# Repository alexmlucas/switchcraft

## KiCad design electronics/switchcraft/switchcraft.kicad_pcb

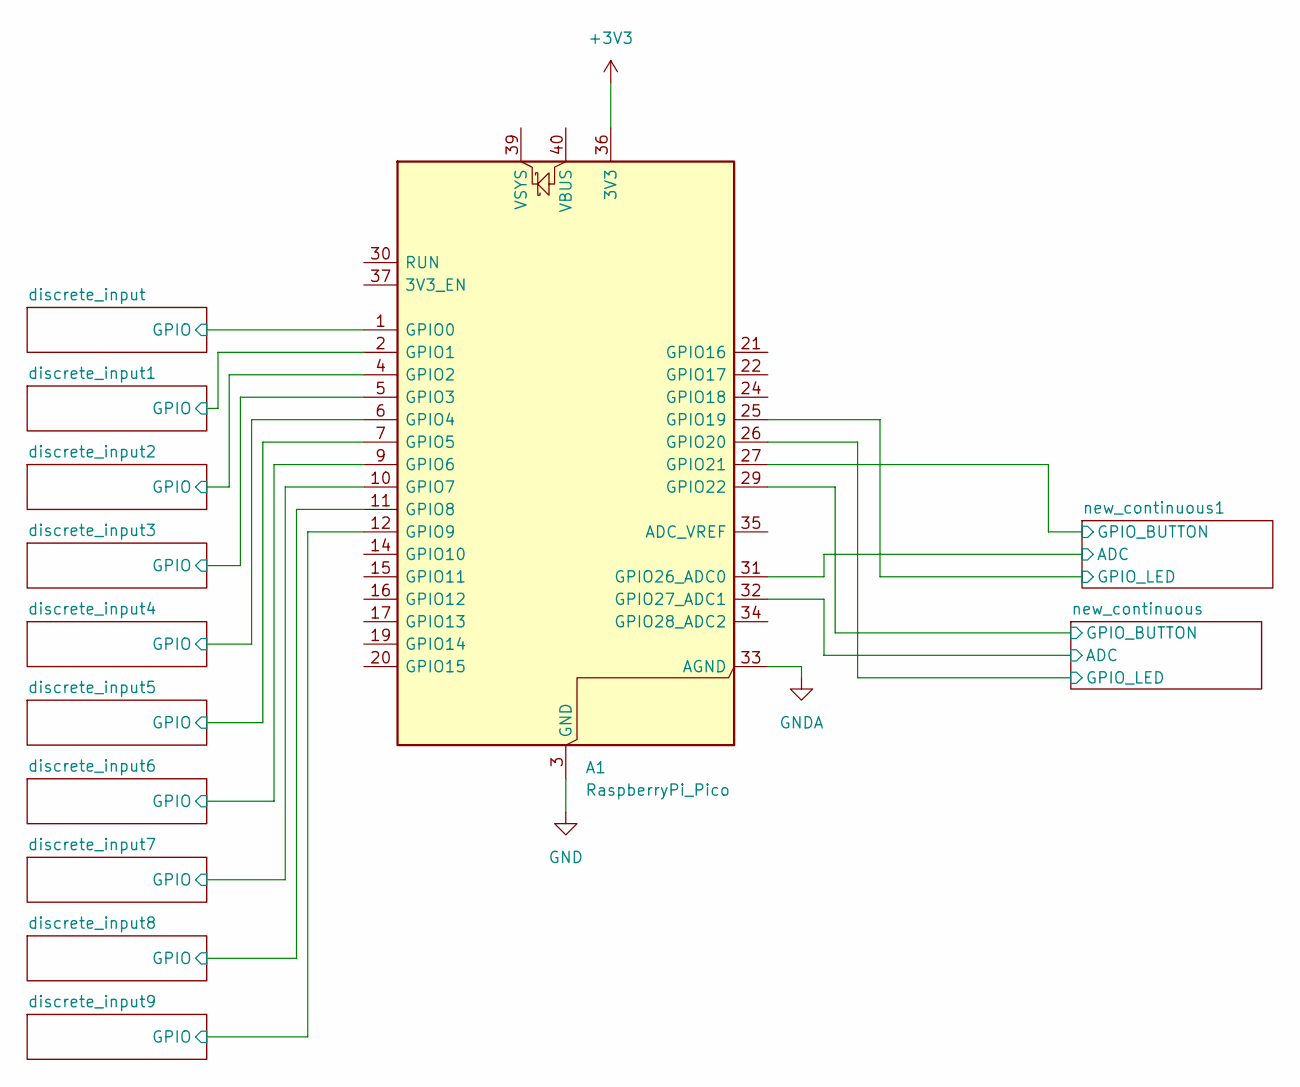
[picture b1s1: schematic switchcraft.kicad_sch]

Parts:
A1: RaspberryPi_Pico; RaspberryPi_Pico_Common_Unspecified

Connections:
+3V3: A1.36 (3V3); also elsewhere on the board
/discrete_input1/GPIO: A1.2 (GPIO1); also elsewhere on the board
/discrete_input2/GPIO: A1.4 (GPIO2); also elsewhere on the board
/discrete_input3/GPIO: A1.5 (GPIO3); also elsewhere on the board
/discrete_input4/GPIO: A1.6 (GPIO4); also elsewhere on the board
/discrete_input5/GPIO: A1.7 (GPIO5); also elsewhere on the board
/discrete_input6/GPIO: A1.9 (GPIO6); also elsewhere on the board
/discrete_input7/GPIO: A1.10 (GPIO7); also elsewhere on the board
/discrete_input8/GPIO: A1.11 (GPIO8); also elsewhere on the board
/discrete_input9/GPIO: A1.12 (GPIO9); also elsewhere on the board
/discrete_input/GPIO: A1.1 (GPIO0); also elsewhere on the board
/new_continuous1/ADC: A1.31 (GPIO26_ADC0); also elsewhere on the board
/new_continuous1/GPIO_BUTTON: A1.27 (GPIO21); also elsewhere on the board
/new_continuous1/GPIO_LED: A1.25 (GPIO19); also elsewhere on the board
/new_continuous/ADC: A1.32 (GPIO27_ADC1); also elsewhere on the board
/new_continuous/GPIO_BUTTON: A1.29 (GPIO22); also elsewhere on the board
/new_continuous/GPIO_LED: A1.26 (GPIO20); also elsewhere on the board
GND: A1.3 (GND), A1.8 (GND), A1.13 (GND), A1.18 (GND), A1.23 (GND), A1.28 (GND), A1.38 (GND); also elsewhere on the board
GNDA: A1.33 (AGND); also elsewhere on the board

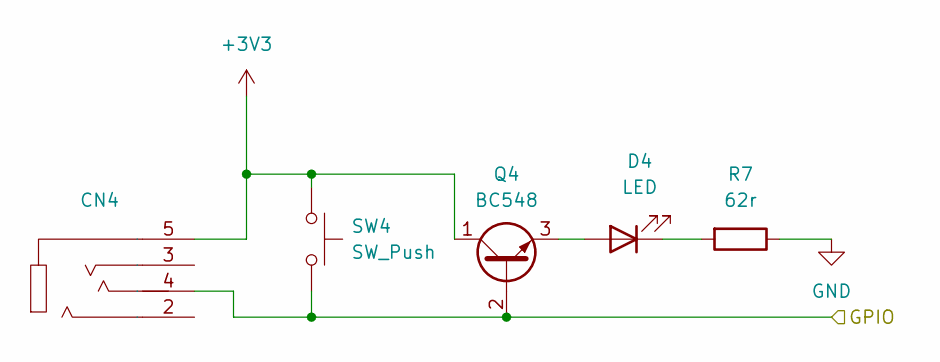
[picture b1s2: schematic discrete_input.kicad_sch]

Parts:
CN4: PJ-320A
D4: LED; LED_D3.0mm
Q4: BC548; TO-92_Inline_Wide
R7: 62r; R_Axial_DIN0207_L6.3mm_D2.5mm_P7.62mm_Horizontal
SW4: SW_Push; SW_PUSH_6mm

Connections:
+3V3: CN4.5, Q4.1 (C), SW4.1; also elsewhere on the board
/discrete_input/GPIO: CN4.4, Q4.2 (B), SW4.2; also elsewhere on the board
GND: R7.1; also elsewhere on the board
unnamed: D4.2 (A), Q4.3 (E)
unnamed: D4.1 (K), R7.2

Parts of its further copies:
CN5, CN6, CN7, CN8, CN9, CN10, CN11, CN12, CN13: PJ-320A
D5, D6, D7, D8, D9, D10, D11, D12, D13: LED; LED_D3.0mm
Q5, Q6, Q7, Q8, Q9, Q10, Q11, Q12, Q13: BC548; TO-92_Inline_Wide
R8, R9, R10, R11, R12, R13, R14, R15, R16: 62r; R_Axial_DIN0207_L6.3mm_D2.5mm_P7.62mm_Horizontal
SW5, SW6, SW7, SW8, SW9, SW10, SW11, SW12, SW13: SW_Push; SW_PUSH_6mm

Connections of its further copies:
+3V3: CN5.5, CN6.5, CN7.5, CN8.5, CN9.5, CN10.5, CN11.5, CN12.5, CN13.5, Q5.1 (C), Q6.1 (C), Q7.1 (C), Q8.1 (C), Q9.1 (C), Q10.1 (C), Q11.1 (C), Q12.1 (C), Q13.1 (C), SW5.1, SW6.1, SW7.1, SW8.1, SW9.1, SW10.1, SW11.1, SW12.1, SW13.1; also elsewhere on the board
/discrete_input1/GPIO: CN5.4, Q5.2 (B), SW5.2; also elsewhere on the board
/discrete_input2/GPIO: CN6.4, Q6.2 (B), SW6.2; also elsewhere on the board
/discrete_input3/GPIO: CN7.4, Q7.2 (B), SW7.2; also elsewhere on the board
/discrete_input4/GPIO: CN8.4, Q8.2 (B), SW8.2; also elsewhere on the board
/discrete_input5/GPIO: CN9.4, Q9.2 (B), SW9.2; also elsewhere on the board
/discrete_input6/GPIO: CN10.4, Q10.2 (B), SW10.2; also elsewhere on the board
/discrete_input7/GPIO: CN11.4, Q11.2 (B), SW11.2; also elsewhere on the board
/discrete_input8/GPIO: CN12.4, Q12.2 (B), SW12.2; also elsewhere on the board
/discrete_input9/GPIO: CN13.4, Q13.2 (B), SW13.2; also elsewhere on the board
GND: R8.1, R9.1, R10.1, R11.1, R12.1, R13.1, R14.1, R15.1, R16.1; also elsewhere on the board
unnamed: D5.2 (A), Q5.3 (E)
unnamed: D5.1 (K), R8.2
unnamed: D6.2 (A), Q6.3 (E)
unnamed: D6.1 (K), R9.2
unnamed: D7.2 (A), Q7.3 (E)
unnamed: D7.1 (K), R10.2
unnamed: D8.2 (A), Q8.3 (E)
unnamed: D8.1 (K), R11.2
unnamed: D9.2 (A), Q13.3 (E)
unnamed: D9.1 (K), R13.2
unnamed: D10.2 (A), Q12.3 (E)
unnamed: D10.1 (K), R14.2
unnamed: D11.2 (A), Q11.3 (E)
unnamed: D11.1 (K), R15.2
unnamed: D12.2 (A), Q9.3 (E)
unnamed: D12.1 (K), R16.2
unnamed: D13.2 (A), Q10.3 (E)
unnamed: D13.1 (K), R12.2

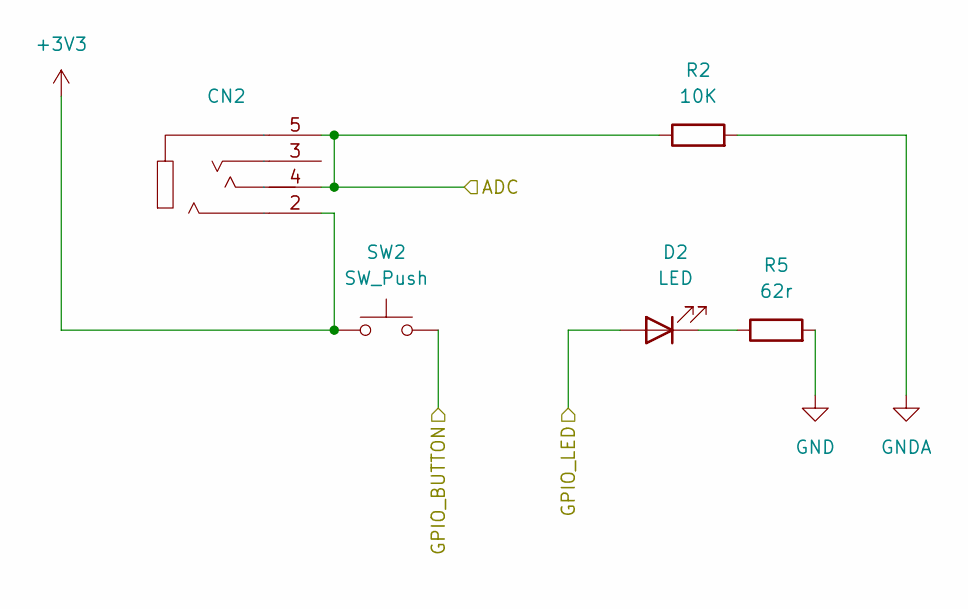
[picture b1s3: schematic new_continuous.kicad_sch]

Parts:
CN2: PJ-320A
D2: LED; LED_D3.0mm
R2: 10K; R_Axial_DIN0207_L6.3mm_D2.5mm_P7.62mm_Horizontal
R5: 62r; R_Axial_DIN0207_L6.3mm_D2.5mm_P7.62mm_Horizontal
SW2: SW_Push; SW_PUSH_6mm

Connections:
+3V3: CN2.2, SW2.1; also elsewhere on the board
/new_continuous1/ADC: CN2.4, CN2.5, R2.1; also elsewhere on the board
/new_continuous1/GPIO_BUTTON: SW2.2; also elsewhere on the board
/new_continuous1/GPIO_LED: D2.2 (A); also elsewhere on the board
GND: R5.2; also elsewhere on the board
GNDA: R2.2; also elsewhere on the board
unnamed: D2.1 (K), R5.1

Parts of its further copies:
CN3: PJ-320A
D19: LED; LED_D3.0mm
R3: 10K; R_Axial_DIN0207_L6.3mm_D2.5mm_P7.62mm_Horizontal
R6: 62r; R_Axial_DIN0207_L6.3mm_D2.5mm_P7.62mm_Horizontal
SW3: SW_Push; SW_PUSH_6mm

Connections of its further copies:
+3V3: CN3.2, SW3.1; also elsewhere on the board
/new_continuous/ADC: CN3.4, CN3.5, R3.1; also elsewhere on the board
/new_continuous/GPIO_BUTTON: SW3.2; also elsewhere on the board
/new_continuous/GPIO_LED: D19.2 (A); also elsewhere on the board
GND: R6.2; also elsewhere on the board
GNDA: R3.2; also elsewhere on the board
unnamed: D19.1 (K), R6.1

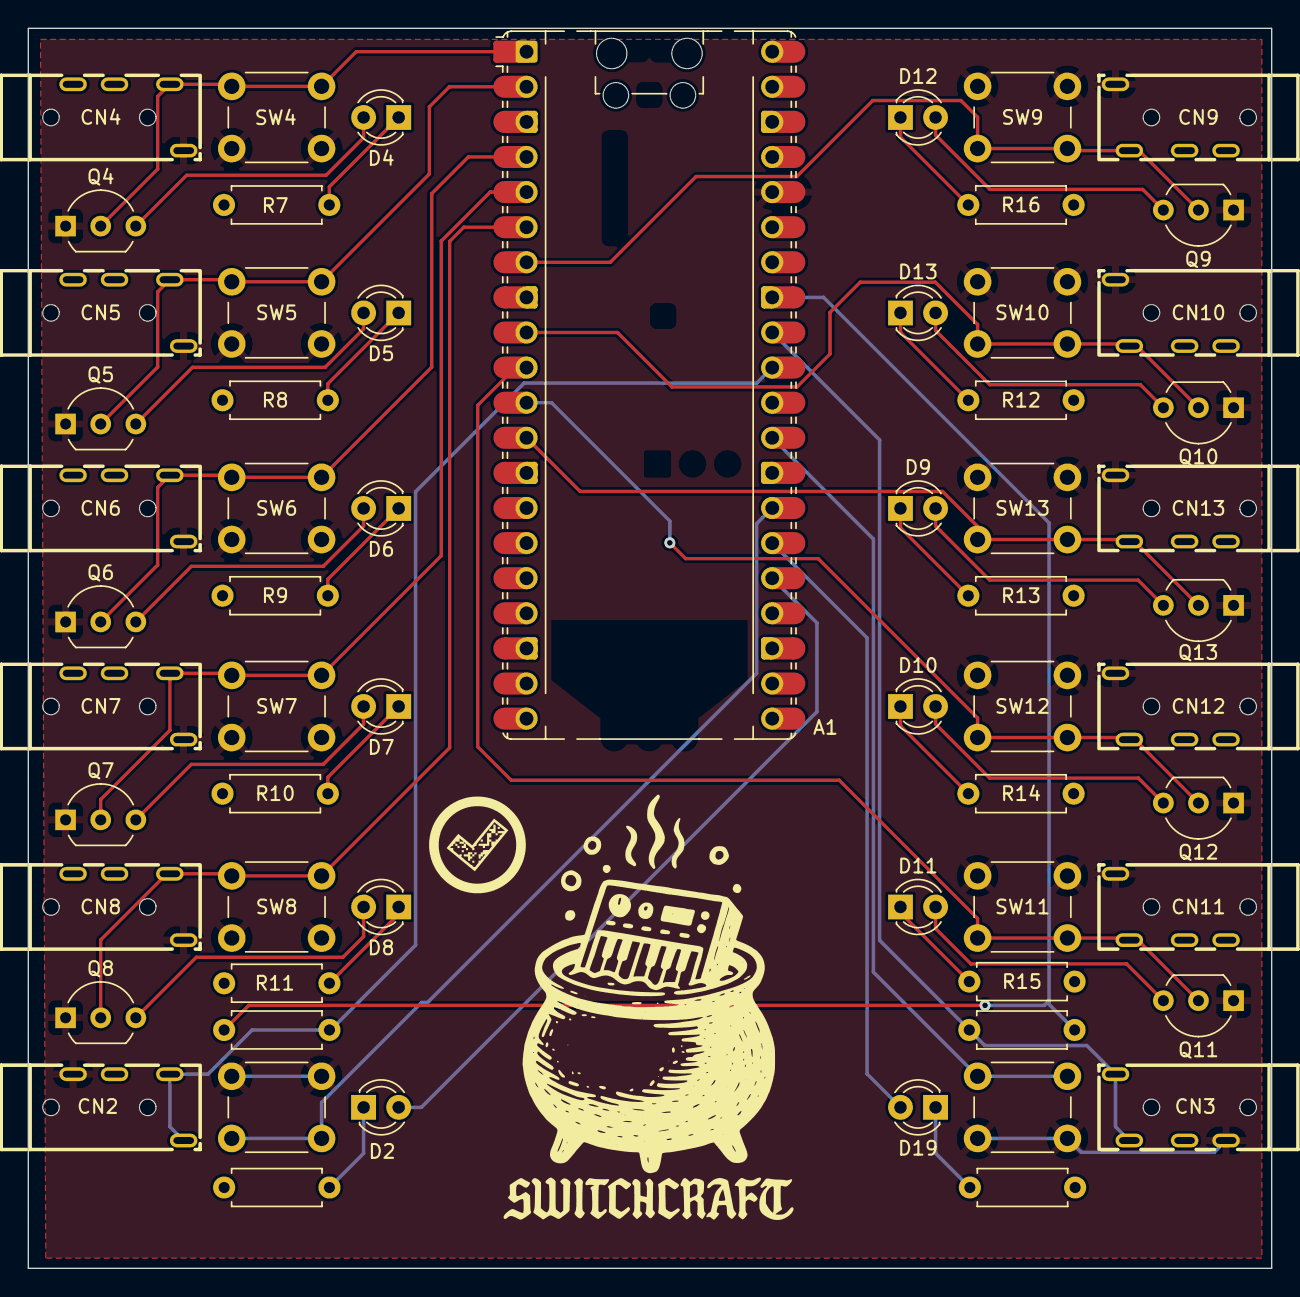
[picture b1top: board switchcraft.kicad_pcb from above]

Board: 2 copper layers, 90.0 x 89.7 mm, 61 parts (0 on the bottom side), 41 nets.

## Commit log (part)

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2025-10-07 general tidy up
2025-12-05 recent update
2025-12-05 add mechanical files
2025-12-11 simplified continuous inputs
